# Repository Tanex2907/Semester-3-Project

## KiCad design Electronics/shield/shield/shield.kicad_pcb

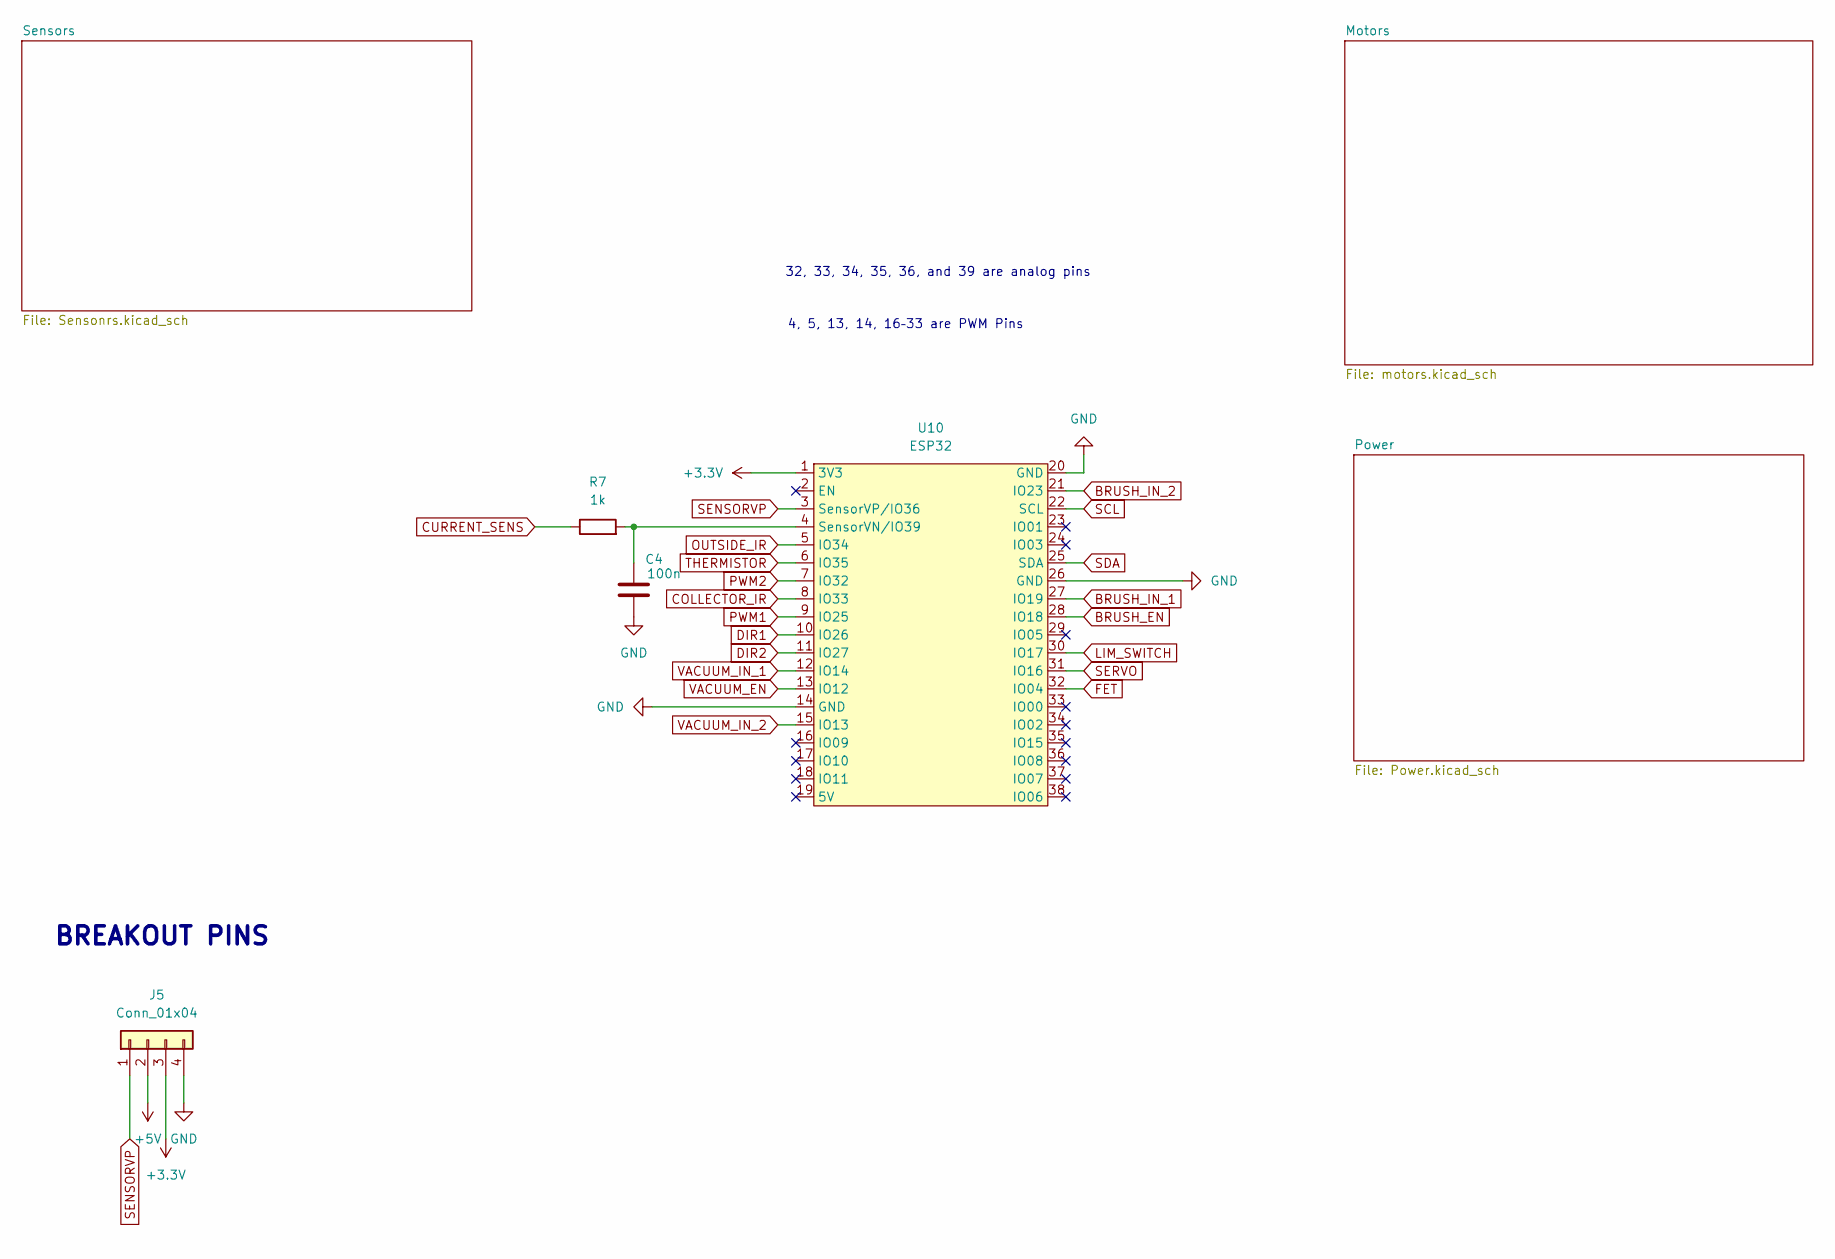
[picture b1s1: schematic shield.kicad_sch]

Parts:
C4: 100n; C_Disc_D5.0mm_W2.5mm_P2.50mm
J5: Conn_01x04; PinHeader_1x04_P2.54mm_Vertical
R7: 1k; R_Axial_DIN0207_L6.3mm_D2.5mm_P10.16mm_Horizontal
U10: ESP32; esp32-38p

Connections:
+3.3V: J5.3, U10.1 (3V3); also elsewhere on the board
+5V: J5.2; also elsewhere on the board
BRUSH_EN: U10.28 (IO18); also elsewhere on the board
BRUSH_IN_1: U10.27 (IO19); also elsewhere on the board
BRUSH_IN_2: U10.21 (IO23); also elsewhere on the board
COLLECTOR_IR: U10.8 (IO33); also elsewhere on the board
CURRENT_SENS: R7.1; also elsewhere on the board
DIR1: U10.10 (IO26); also elsewhere on the board
DIR2: U10.11 (IO27); also elsewhere on the board
FET: U10.32 (IO04); also elsewhere on the board
GND: C4.2, J5.4, U10.14 (GND), U10.20 (GND), U10.26 (GND); also elsewhere on the board
LIM_SWITCH: U10.30 (IO17); also elsewhere on the board
unnamed: C4.1, R7.2, U10.4 (SensorVN/IO39)
OUTSIDE_IR: U10.5 (IO34); also elsewhere on the board
PWM1: U10.9 (IO25); also elsewhere on the board
PWM2: U10.7 (IO32); also elsewhere on the board
SCL: U10.22 (SCL); also elsewhere on the board
SDA: U10.25 (SDA); also elsewhere on the board
SENSORVP: J5.1, U10.3 (SensorVP/IO36)
SERVO: U10.31 (IO16); also elsewhere on the board
THERMISTOR: U10.6 (IO35); also elsewhere on the board
VACUUM_EN: U10.13 (IO12); also elsewhere on the board
VACUUM_IN_1: U10.12 (IO14); also elsewhere on the board
VACUUM_IN_2: U10.15 (IO13); also elsewhere on the board

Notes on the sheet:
BREAKOUT PINS
4, 5, 13, 14, 16–33 are PWM Pins
32, 33, 34, 35, 36, and 39 are analog pins

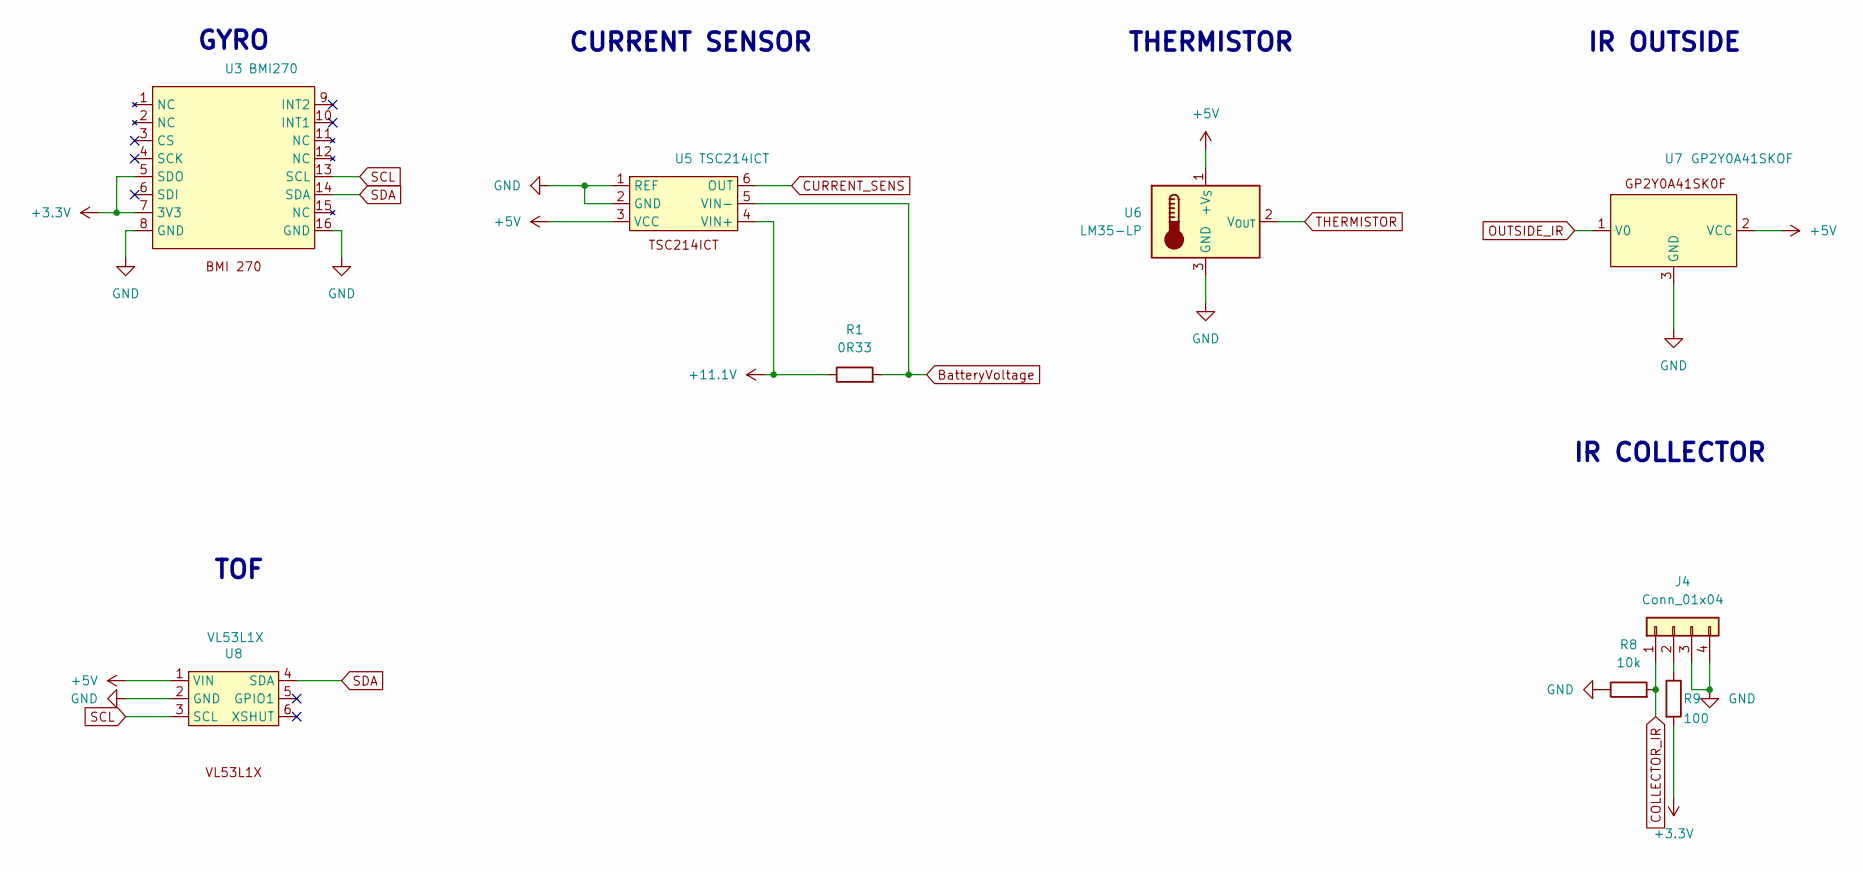
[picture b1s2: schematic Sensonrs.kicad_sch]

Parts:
J4: Conn_01x04; JST_XH_B4B-XH-A_1x04_P2.50mm_Vertical
R1: 0R33; R_Axial_DIN0207_L6.3mm_D2.5mm_P10.16mm_Horizontal
R8: 10k; R_Axial_DIN0207_L6.3mm_D2.5mm_P10.16mm_Horizontal
R9: 100; R_Axial_DIN0207_L6.3mm_D2.5mm_P10.16mm_Horizontal
U3: BMI270
U5: TSC214ICT; SOT-363_SC-70-6
U6: LM35-LP; JST_XH_B3B-XH-A_1x03_P2.50mm_Vertical
U7: GP2Y0A41SKOF; JST_XH_B3B-XH-A_1x03_P2.50mm_Vertical
U8: VL53L1X; JST_XH_B4B-XH-A_1x04_P2.50mm_Vertical

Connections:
+3.3V: R9.2, U3.5 (SDO), U3.7 (3V3); also elsewhere on the board
+5V: U5.3 (VCC), U6.1 (+V_{S}), U7.2 (VCC), U8.1 (VIN); also elsewhere on the board
+11.1V: R1.1, U5.4 (VIN+); also elsewhere on the board
BatteryVoltage: R1.2, U5.5 (VIN-); also elsewhere on the board
COLLECTOR_IR: J4.1, R8.2; also elsewhere on the board
CURRENT_SENS: U5.6 (OUT); also elsewhere on the board
GND: J4.3, J4.4, R8.1, U3.8 (GND), U3.16 (GND), U5.1 (REF), U5.2 (GND), U6.3 (GND), U7.3 (GND), U8.2 (GND); also elsewhere on the board
unnamed: J4.2, R9.1
OUTSIDE_IR: U7.1 (V0); also elsewhere on the board
SCL: U3.13 (SCL), U8.3 (SCL); also elsewhere on the board
SDA: U3.14 (SDA), U8.4 (SDA); also elsewhere on the board
THERMISTOR: U6.2 (V_{OUT}); also elsewhere on the board

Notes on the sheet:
CURRENT SENSOR
IR OUTSIDE
GYRO
IR COLLECTOR
TOF
THERMISTOR

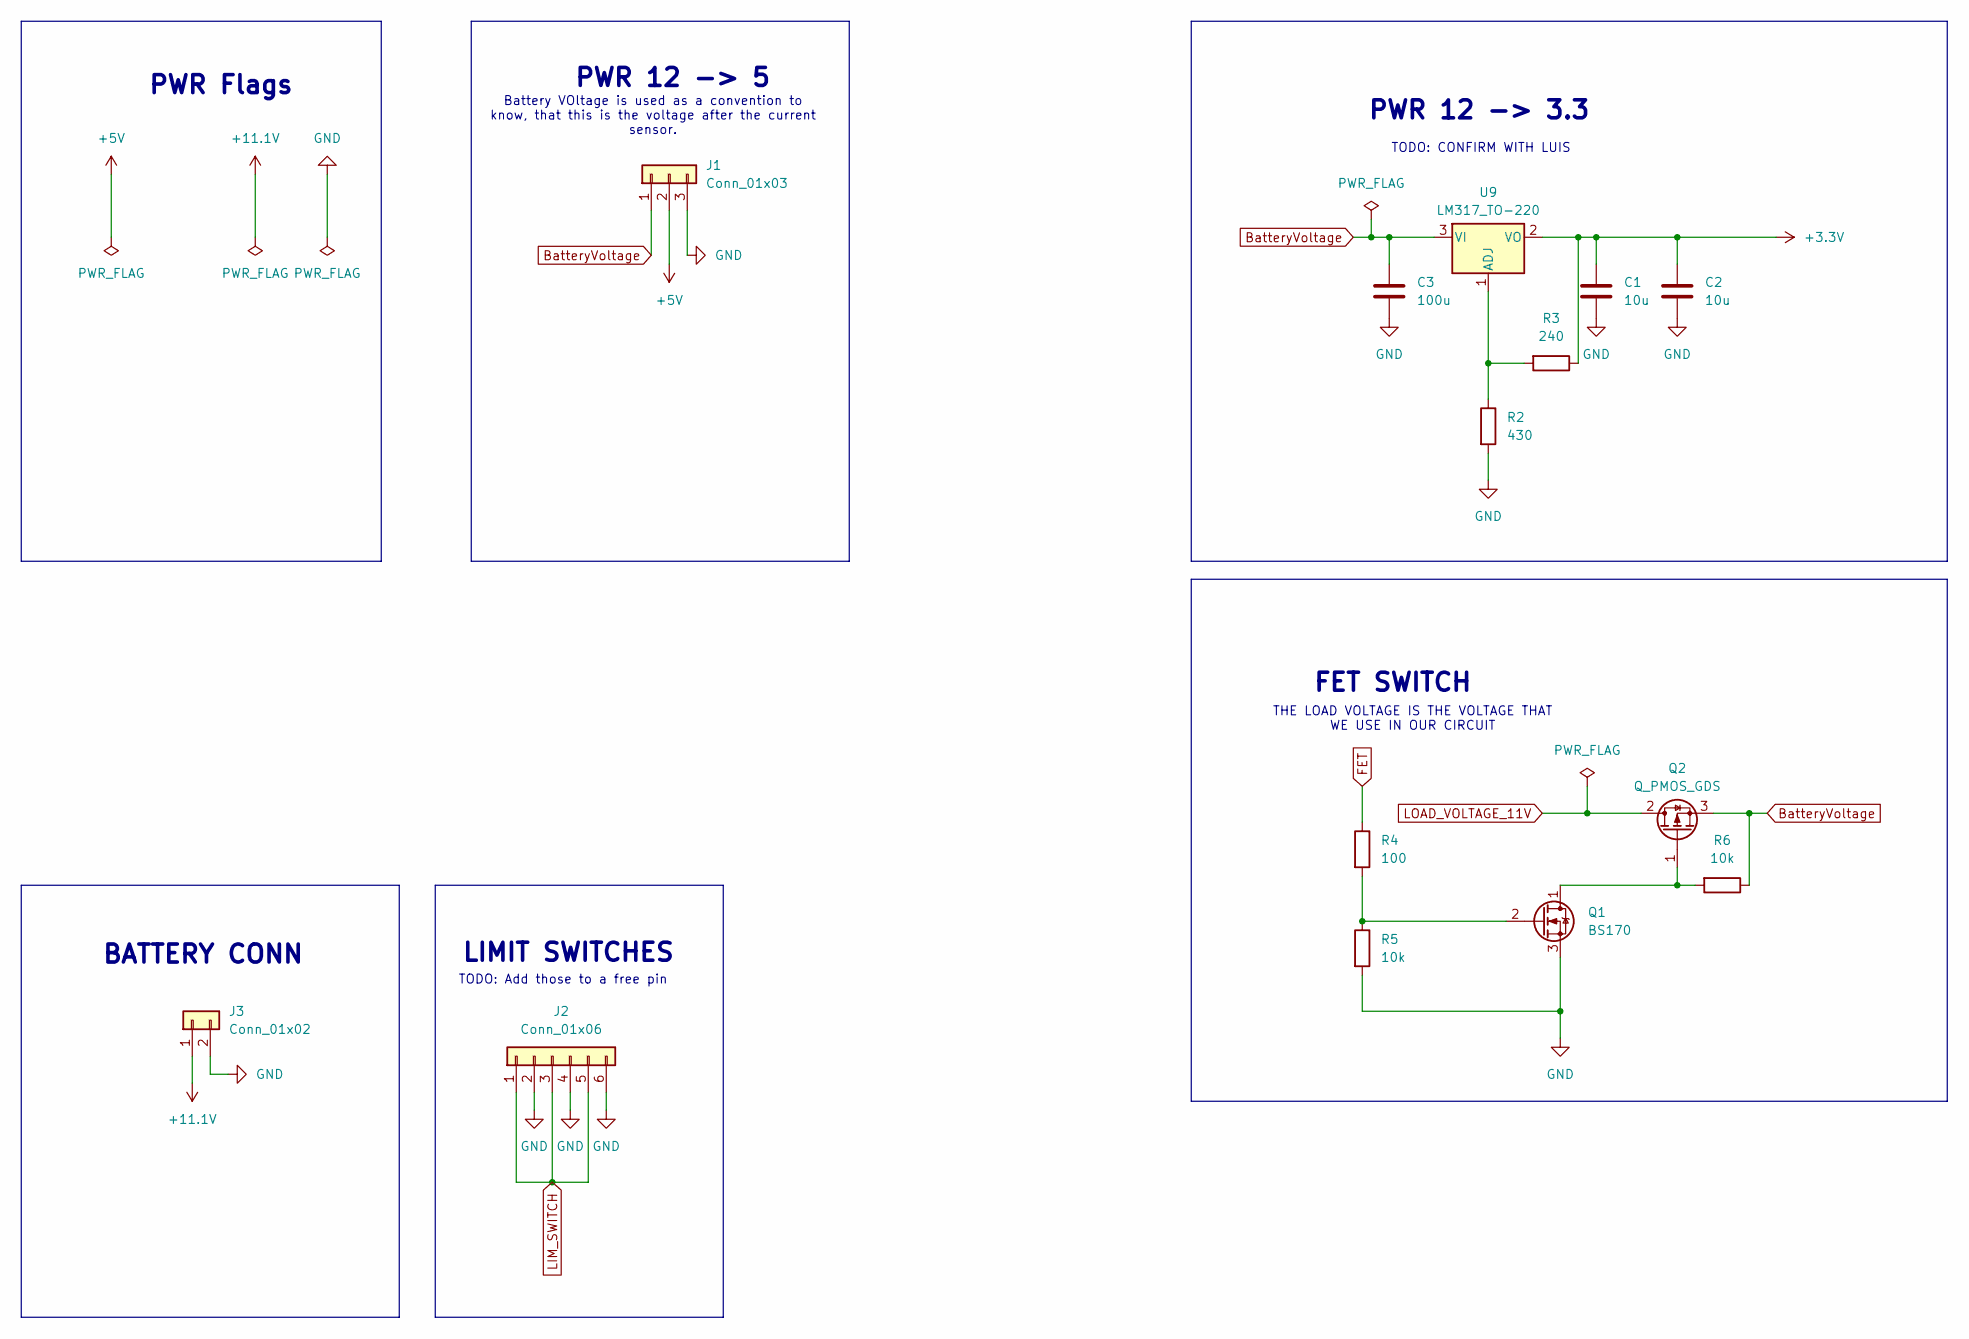
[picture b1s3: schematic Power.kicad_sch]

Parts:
C1, C2: 10u; C_Disc_D5.0mm_W2.5mm_P2.50mm
C3: 100u; C_Disc_D5.0mm_W2.5mm_P2.50mm
J1: Conn_01x03; JST_XH_B3B-XH-A_1x03_P2.50mm_Vertical
J2: Conn_01x06; JST_XH_B6B-XH-A_1x06_P2.50mm_Vertical
J3: Conn_01x02; JST_XH_B2B-XH-A_1x02_P2.50mm_Vertical
Q1: BS170; TO-92_HandSolder
Q2: Q_PMOS_GDS; TO-220-3_Vertical
R2: 430; R_Axial_DIN0207_L6.3mm_D2.5mm_P10.16mm_Horizontal
R3: 240; R_Axial_DIN0207_L6.3mm_D2.5mm_P10.16mm_Horizontal
R4: 100; R_Axial_DIN0207_L6.3mm_D2.5mm_P10.16mm_Horizontal
R5, R6: 10k; R_Axial_DIN0207_L6.3mm_D2.5mm_P10.16mm_Horizontal
U9: LM317_TO-220; TO-220-3_Vertical

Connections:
+3.3V: C1.1, C2.1, R3.1, U9.2 (VO); also elsewhere on the board
+5V: J1.2; also elsewhere on the board
+11.1V: J3.1; also elsewhere on the board
BatteryVoltage: C3.1, J1.1, Q2.3 (S), R6.1, U9.3 (VI); also elsewhere on the board
FET: R4.1; also elsewhere on the board
GND: C1.2, C2.2, C3.2, J1.3, J2.2, J2.4, J2.6, J3.2, Q1.3 (S), R2.2, R5.2; also elsewhere on the board
LIM_SWITCH: J2.1, J2.3, J2.5; also elsewhere on the board
LOAD_VOLTAGE_11V: Q2.2 (D); also elsewhere on the board
unnamed: Q1.1 (D), Q2.1 (G), R6.2
unnamed: Q1.2 (G), R4.2, R5.1
unnamed: R2.1, R3.2, U9.1 (ADJ)

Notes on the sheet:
TODO: CONFIRM WITH LUIS
THE LOAD VOLTAGE IS THE VOLTAGE THAT WE USE IN OUR CIRCUIT
PWR Flags
BATTERY CONN
FET SWITCH
LIMIT SWITCHES
PWR 12 -> 5
PWR 12 -> 3.3
TODO: Add those to a free pin
Battery VOltage is used as a convention to know, that this is the voltage after the current sensor.

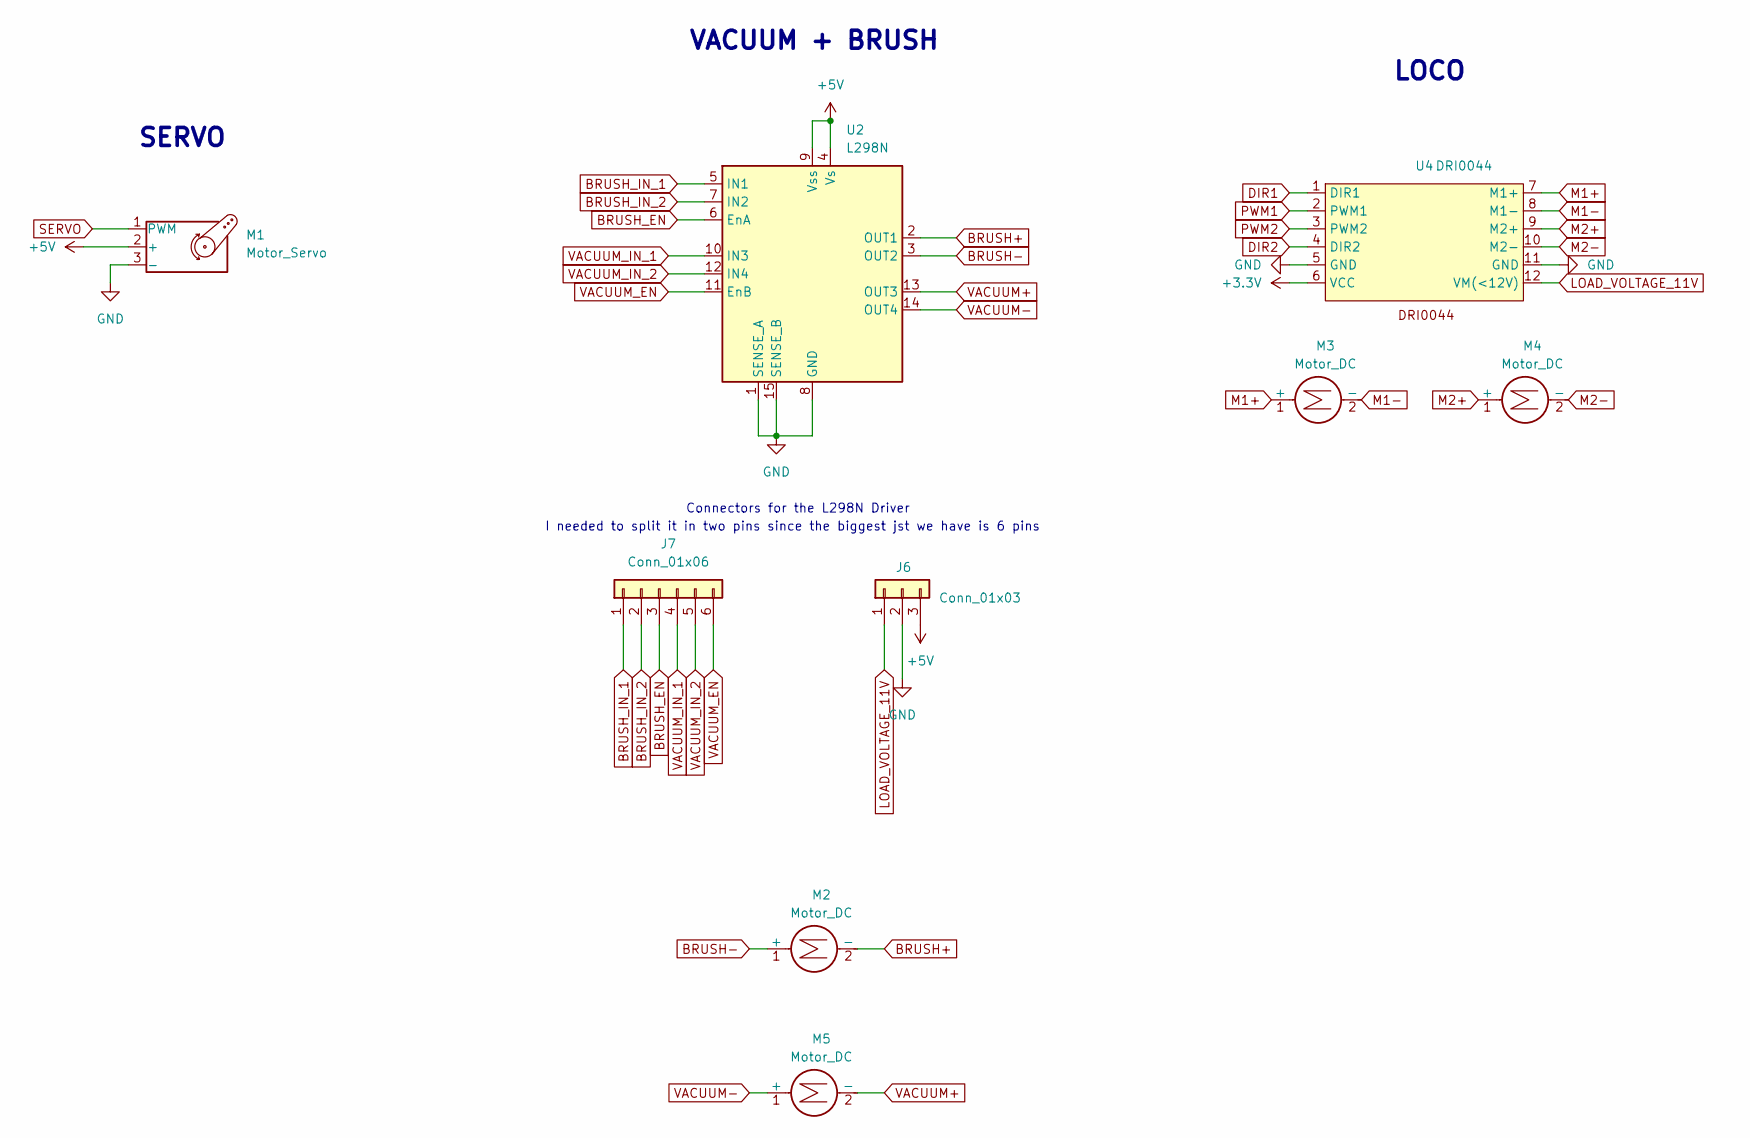
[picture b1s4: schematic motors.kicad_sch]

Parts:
J6: Conn_01x03; JST_EH_B3B-EH-A_1x03_P2.50mm_Vertical
J7: Conn_01x06; JST_XH_B6B-XH-A_1x06_P2.50mm_Vertical
M1: Motor_Servo; JST_XH_B3B-XH-A_1x03_P2.50mm_Vertical
M2, M5: Motor_DC
M3, M4: Motor_DC; JST_XH_B2B-XH-A_1x02_P2.50mm_Vertical
U2: L298N; TO-220-15_P2.54x5.08mm_StaggerOdd_Lead4.58mm_Vertical
U4: DRI0044

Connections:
+3.3V: U4.6 (VCC); also elsewhere on the board
+5V: J6.3, M1.2 (+), U2.4 (Vs), U2.9 (Vss); also elsewhere on the board
BRUSH_EN: J7.3, U2.6 (EnA); also elsewhere on the board
BRUSH_IN_1: J7.1, U2.5 (IN1); also elsewhere on the board
BRUSH_IN_2: J7.2, U2.7 (IN2); also elsewhere on the board
DIR1: U4.1 (DIR1); also elsewhere on the board
DIR2: U4.4 (DIR2); also elsewhere on the board
GND: J6.2, M1.3 (-), U2.1 (SENSE_A), U2.8 (GND), U2.15 (SENSE_B), U4.5 (GND), U4.11 (GND); also elsewhere on the board
LOAD_VOLTAGE_11V: J6.1, U4.12 (VM(<12V)); also elsewhere on the board
M1+: M3.1 (+), U4.7 (M1+)
M1-: M3.2 (-), U4.8 (M1-)
M2+: M4.1 (+), U4.9 (M2+)
M2-: M4.2 (-), U4.10 (M2-)
unnamed: M2.1 (+), U2.3 (OUT2)
unnamed: M2.2 (-), U2.2 (OUT1)
unnamed: M5.1 (+), U2.14 (OUT4)
unnamed: M5.2 (-), U2.13 (OUT3)
PWM1: U4.2 (PWM1); also elsewhere on the board
PWM2: U4.3 (PWM2); also elsewhere on the board
SERVO: M1.1 (PWM); also elsewhere on the board
VACUUM_EN: J7.6, U2.11 (EnB); also elsewhere on the board
VACUUM_IN_1: J7.4, U2.10 (IN3); also elsewhere on the board
VACUUM_IN_2: J7.5, U2.12 (IN4); also elsewhere on the board

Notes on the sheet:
I needed to split it in two pins since the biggest jst we have is 6 pins
Connectors for the L298N Driver
SERVO
VACUUM + BRUSH
LOCO

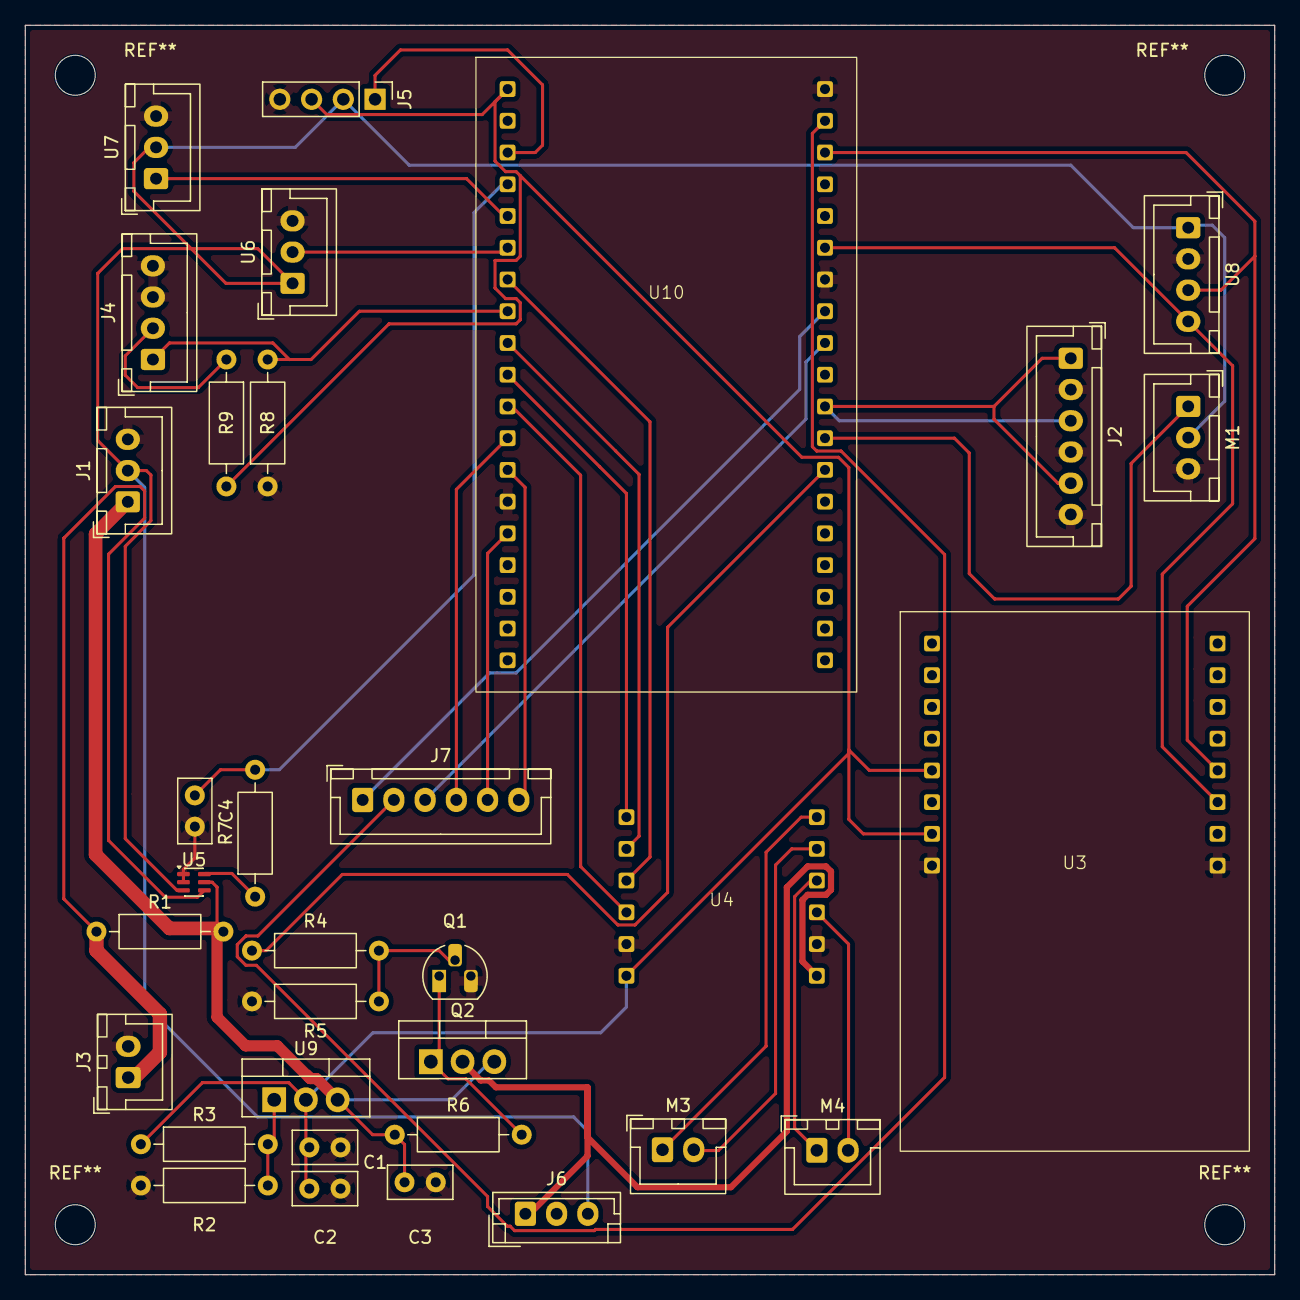
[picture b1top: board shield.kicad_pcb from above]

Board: 2 copper layers, 100.0 x 100.0 mm, 33 parts (0 on the bottom side), 35 nets.

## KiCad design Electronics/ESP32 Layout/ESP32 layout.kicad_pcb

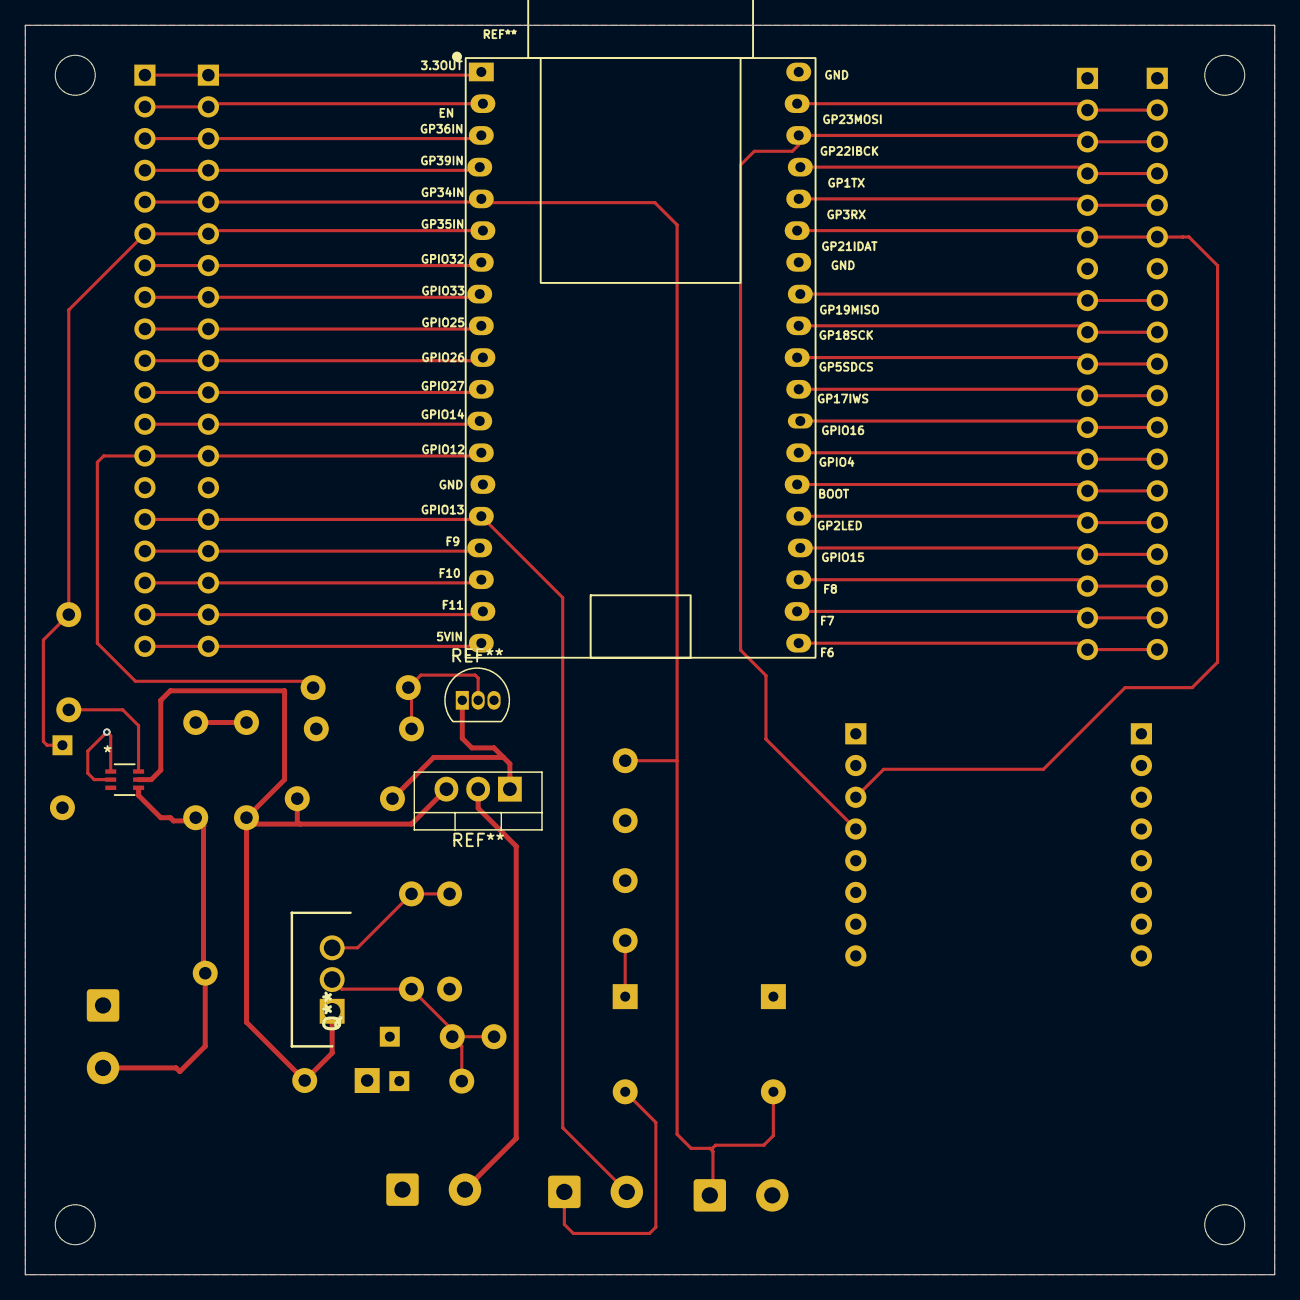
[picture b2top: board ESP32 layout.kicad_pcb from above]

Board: 2 copper layers, 100.0 x 100.0 mm, 27 parts (0 on the bottom side), 11 nets.

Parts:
C1, C3, C4: 100u; C_Disc_D5.0mm_W2.5mm_P5.00mm
C2: 10u; C_Disc_D5.0mm_W2.5mm_P5.00mm
H1, H2, H3, H4: MountingHole_3.2mm_M3
J1, J1#2: IR_LED (OPB100-EZ); TerminalBlock_Phoenix_MKDS-1,5-2_1x02_P5.00mm_Horizontal
J2: IR_SENSOR (OPB100-SZ); TerminalBlock_Phoenix_MKDS-1,5-2_1x02_P5.00mm_Horizontal
Q**: LM317T
R1, R3, R8, R9: 240; R_Axial_DIN0207_L6.3mm_D2.5mm_P7.62mm_Horizontal
R2: 390; R_Axial_DIN0207_L6.3mm_D2.5mm_P7.62mm_Horizontal
R4, R7: 10k; R_Axial_DIN0207_L6.3mm_D2.5mm_P7.62mm_Horizontal
R5, R6: 100; R_Axial_DIN0207_L6.3mm_D2.5mm_P7.62mm_Horizontal
R10: 1k; R_Axial_DIN0207_L6.3mm_D2.5mm_P7.62mm_Horizontal
TP1, TP2, TP3, TP4, TP5: TestPoint; TestPoint_THTPad_D2.0mm_Drill1.0mm

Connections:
3.3V: R6.1, R7.1, TP1.1
12V: C3.2, Q**.1, R3.Test Shunt-, R9.Shunt-
12V_IN: R8.2, TP2.1
Current_sensor: C4.1, R10.1
GATE_1: R4.2, R5.2
GND: C1.1, C2.1, C3.e, C4.2, J2.2, R2.2, R4.1, TP3.1, TP4.1
IR_LED_A: J1#2.1, R6.2
IR_SENSE: J2.1, R7.2, TP5.1
LM317ADJUST: Q**.3, R1.1, R2.1
LM317OUT: C1.2, C2.2, Q**.2, R1.2
rshunt: R8.1, R9.1
